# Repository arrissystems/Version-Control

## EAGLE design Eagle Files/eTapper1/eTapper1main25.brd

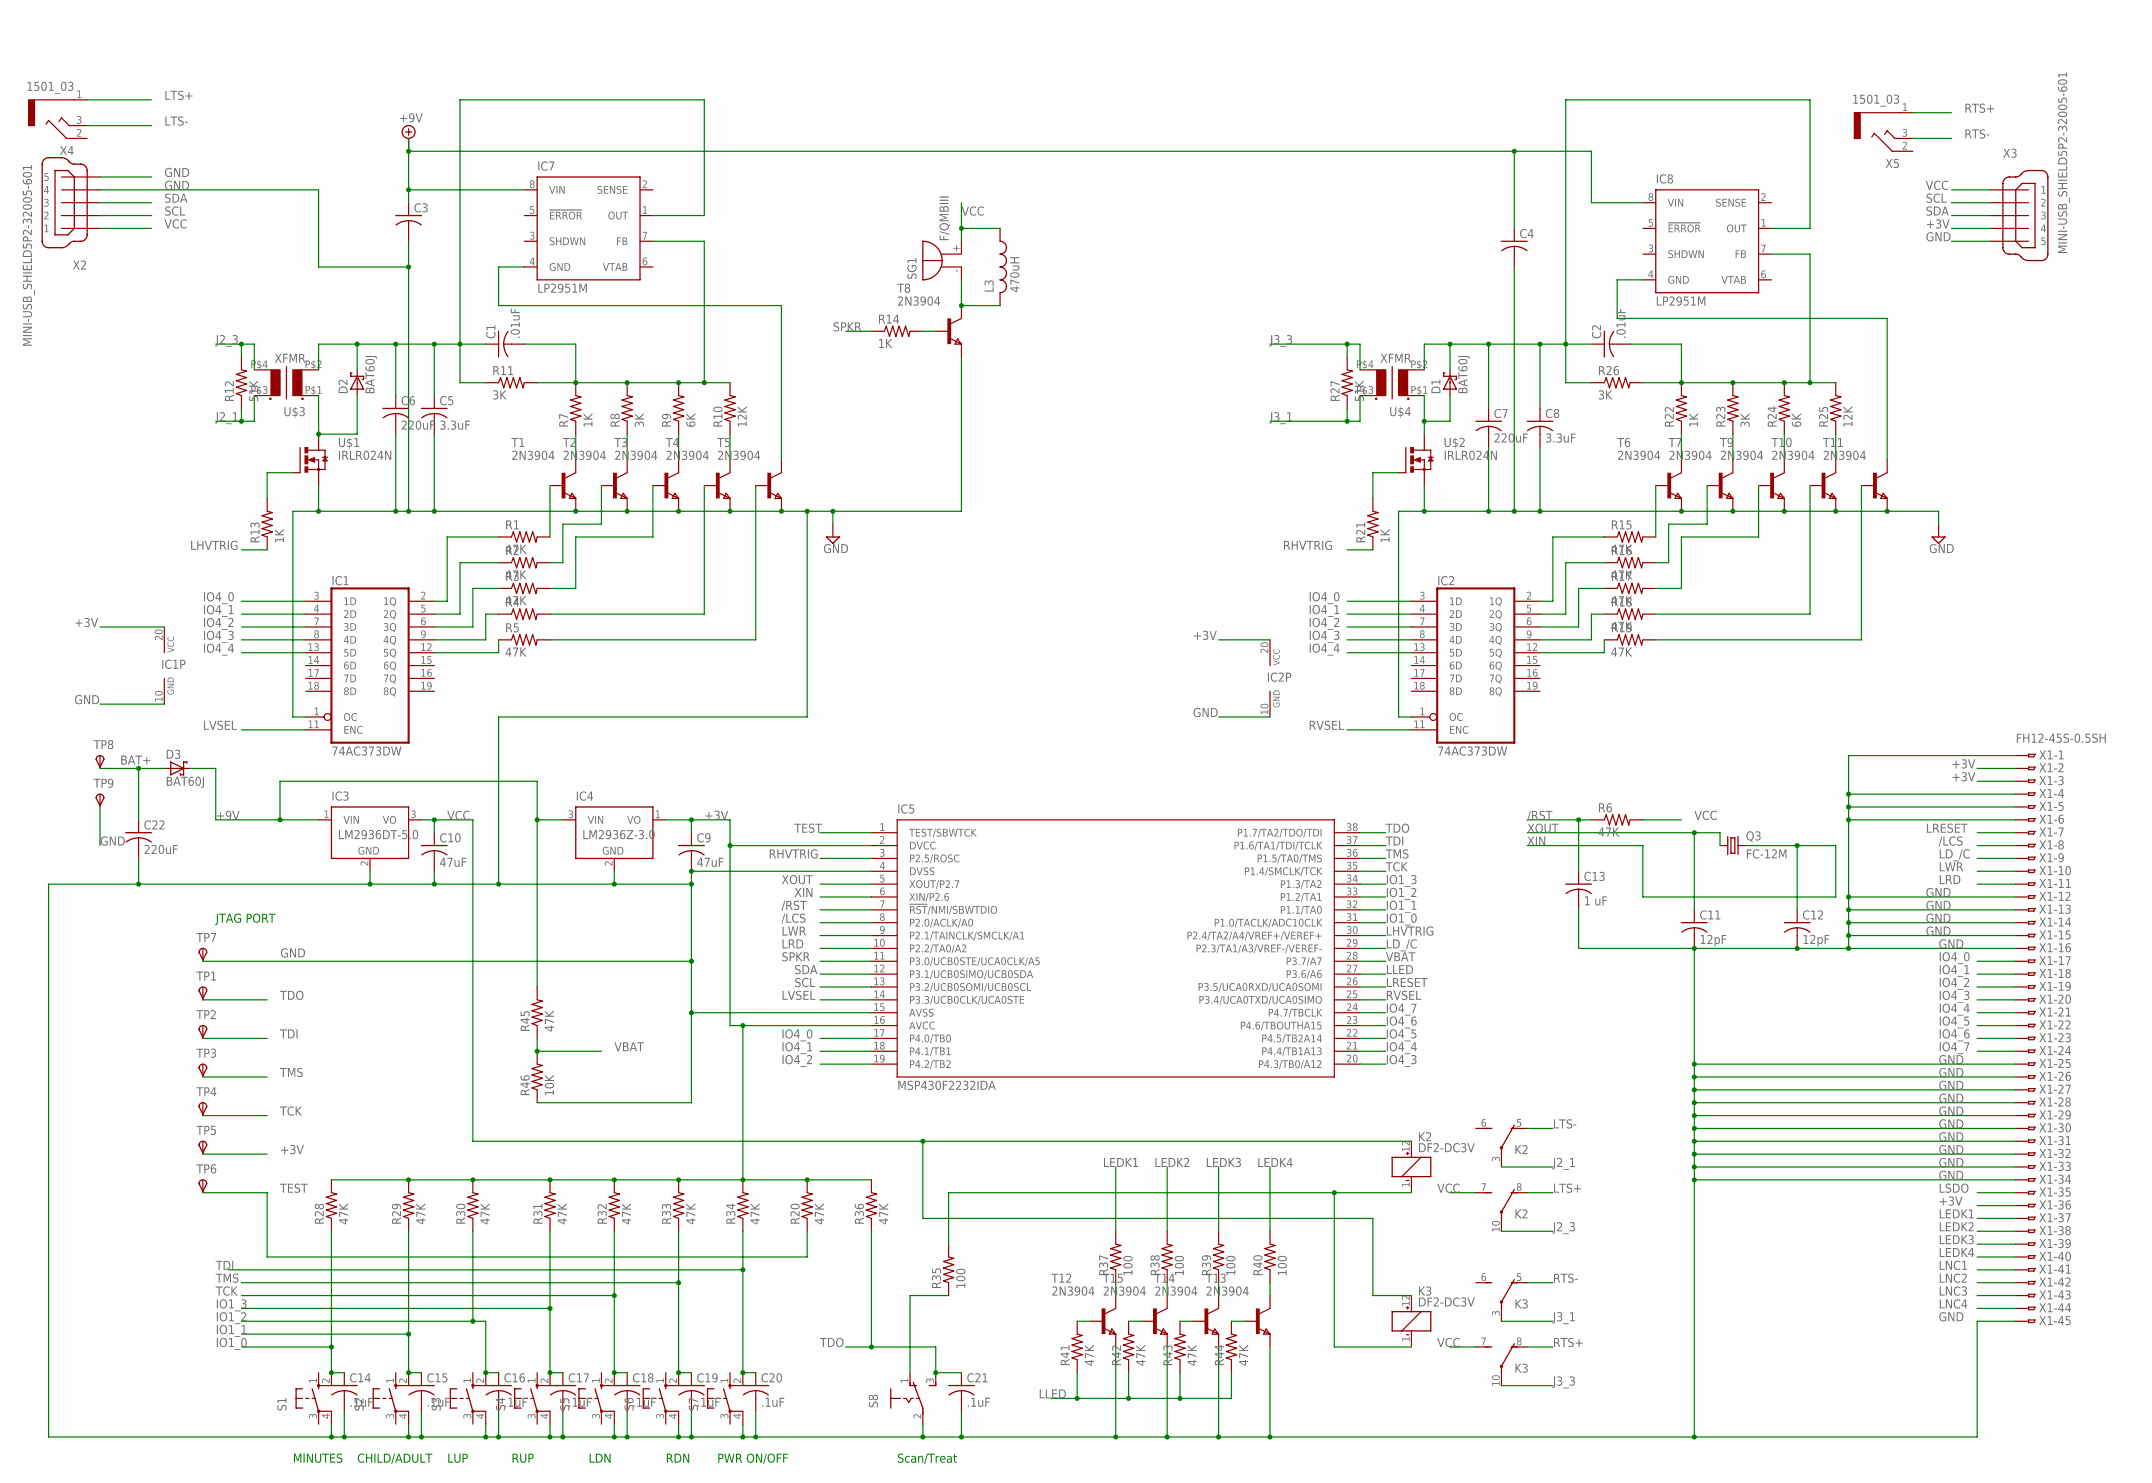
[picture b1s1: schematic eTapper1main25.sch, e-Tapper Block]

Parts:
C1, C2: .01uF; C0805
C3, C4: C-USC0805; C0805
C5, C8: 3.3uF; C0805
C6, C7, C22: 220uF; C0805
C9, C10: 47uF; C0805
C11, C12: 12pF; C0805
C13: 1 uF; C0805
C14, C15, C16, C17, C18, C19, C20, C21: .1uF; C0805
D1, D2, D3: BAT60J; SOD323_ST
IC1, IC2: 74AC373DW; SO20W
IC3: LM2936DT-5.0; TO252
IC4: LM2936Z-3.0; TO92
IC5: MSP430F2232IDA; TSSOP38_R-PDSO-G38-DA
IC7, IC8: LP2951M; SO08
K2, K3: DF2-DC3V; DF2
L3: 470uH; L2825P
Q3: FC-12M
R1, R2, R3, R5, R6, R15, R16, R17, R18, R19, R20, R28, R29, R30, R31, R32, R33, R34, R36, R41, R42, R43, R44, R45: 47K; R0402
R4: R-US_R0402; R0402
R7, R13, R14, R21, R22: 1K; R0402
R8, R11, R23, R26: 3K; R0402
R9, R24: 6K; R0402
R10, R25: 12K; R0402
R12, R27: 51K; R0402
R35, R37, R38, R39, R40: 100; R0402
R46: 10K; R0402
S1, S2, S3, S4, S5, S6, S7: 10-XX; B3F-10XX
S8: M251
SG1: F/QMBIII
T1, T2, T3, T4, T5, T6, T7, T8, T9, T10, T11, T12, T13, T14, T15: 2N3904; SOT-23
TP1, TP2, TP3, TP4, TP5, TP6, TP7, TP8, TP9: TPSTP06R; TP06R
U$1, U$2: IRLR024N; D-PAK_TO252AA
U$3, U$4: XFMR
X1: FH12-45S-0.5SH
X2, X3: MINI-USB_SHIELD5P2-32005-601; 32005-601
X4, X5: 1501_03

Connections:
+3V: C9.1, IC1.20 (VCC), IC2.20 (VCC), IC4.1 (VO), IC5.2 (DVCC), IC5.16 (AVCC), R20.2, R28.2, R29.2, R30.2, R31.2, R32.2, R33.2, R34.2, R36.2, TP5.TP, X1.2, X1.3, X1.36, X3.4
+9V: C3.1, C4.1, D3.C, IC3.1 (VIN), IC4.3 (VIN), IC7.8 (VIN), IC8.8 (VIN), R45.2
/LCS: IC5.8 (P2.0/ACLK/A0), X1.8
/RST: C13.1, IC5.7 (!RST!/NMI/SBWTDIO), R6.1
BAT+: C22.1, D3.A, TP8.TP
GND: C3.2, C4.2, C5.2, C6.2, C7.2, C8.2, C9.2, C10.2, C11.2, C12.2, C13.2, C14.2, C15.2, C16.2, C17.2, C18.2, C19.2, C20.2, C21.2, C22.2, IC1.1 (OC), IC1.10 (GND), IC2.1 (OC), IC2.10 (GND), IC3.2 (GND), IC4.2 (GND), IC5.4 (DVSS), IC5.15 (AVSS), R46.1, S1.4 (P1), S2.4 (P1), S3.4 (P1), S4.4 (P1), S5.4 (P1), S6.4 (P1), S7.4 (P1), S8.2, T1.2 (E), T2.2 (E), T3.2 (E), T4.2 (E), T5.2 (E), T6.2 (E), T7.2 (E), T8.2 (E), T9.2 (E), T10.2 (E), T11.2 (E), T12.2 (E), T13.2 (E), T14.2 (E), T15.2 (E), TP7.TP, TP9.TP, U$1.3 (S), U$2.3 (S), X1.1, X1.4, X1.5, X1.6, X1.12, X1.13, X1.14, X1.15, X1.16, X1.25, X1.26, X1.27, X1.28, X1.29, X1.30, X1.31, X1.32, X1.33, X1.34, X1.45, X2.4, X2.5, X3.5
IO1_0: C14.1, IC5.31 (P1.0/TACLK/ADC10CLK), R28.1, S1.2 (S1)
IO1_1: C15.1, IC5.32 (P1.1/TA0), R29.1, S2.2 (S1)
IO1_2: C16.1, IC5.33 (P1.2/TA1), R30.1, S3.2 (S1)
IO1_3: C17.1, IC5.34 (P1.3/TA2), R31.1, S4.2 (S1)
IO4_0: IC1.3 (1D), IC2.3 (1D), IC5.17 (P4.0/TB0), X1.17
IO4_1: IC1.4 (2D), IC2.4 (2D), IC5.18 (P4.1/TB1), X1.18
IO4_2: IC1.7 (3D), IC2.7 (3D), IC5.19 (P4.2/TB2), X1.19
IO4_3: IC1.8 (4D), IC2.8 (4D), IC5.20 (P4.3/TB0/A12), X1.20
IO4_4: IC1.13 (5D), IC2.13 (5D), IC5.21 (P4.4/TB1A13), X1.21
IO4_5: IC5.22 (P4.5/TB2A14), X1.22
IO4_6: IC5.23 (P4.6/TBOUTHA15), X1.23
IO4_7: IC5.24 (P4.7/TBCLK), X1.24
J2_1: K2.3, R12.1, U$3.P$3 (S1)
J2_3: K2.10, R12.2, U$3.P$4 (S2)
J3_1: K3.3, R27.1, U$4.P$3 (S1)
J3_3: K3.10, R27.2, U$4.P$4 (S2)
LD_/C: IC5.29 (P2.3/TA1/A3/VREF-/VEREF-), X1.9
LEDK1: R37.2, X1.37
LEDK2: R38.2, X1.38
LEDK3: R39.2, X1.39
LEDK4: R40.2, X1.40
LHVTRIG: IC5.30 (P2.4/TA2/A4/VREF+/VEREF+), R13.1
LLED: IC5.27 (P3.6/A6), R41.1, R42.1, R43.1, R44.1
LNC1: X1.41
LNC2: X1.42
LNC3: X1.43
LNC4: X1.44
LRD: IC5.10 (P2.2/TA0/A2), X1.11
LRESET: IC5.26 (P3.5/UCA0RXD/UCA0SOMI), X1.7
LSDO: X1.35
LTS+: K2.8 (O), X4.1
LTS-: K2.5 (O), X4.3
LVSEL: IC1.11 (ENC), IC5.14 (P3.3/UCB0CLK/UCA0STE)
LWR: IC5.9 (P2.1/TAINCLK/SMCLK/A1), X1.10
unnamed: IC1.2 (1Q), R1.1
unnamed: IC1.5 (2Q), R2.1
unnamed: IC1.6 (3Q), R3.1
unnamed: IC1.9 (4Q), R4.1
unnamed: IC1.12 (5Q), R5.1
unnamed: L3.2, SG1.- (+), T8.1 (C)
unnamed: R4.2, T4.3 (B)
unnamed: R5.2, T5.3 (B)
unnamed: D2.A, U$1.4 (D), U$3.P$1 (P1)
unnamed: R7.1, T1.1 (C)
unnamed: R8.1, T2.1 (C)
unnamed: R9.1, T3.1 (C)
unnamed: R1.2, T1.3 (B)
unnamed: R2.2, T2.3 (B)
unnamed: R3.2, T3.3 (B)
unnamed: R10.1, T4.1 (C)
unnamed: C1.2, IC7.7 (FB), R7.2, R8.2, R9.2, R10.2, R11.2
unnamed: C1.1, C5.1, C6.1, D2.C, IC7.1 (OUT), R11.1, U$3.P$2 (P2)
unnamed: D1.A, U$2.4 (D), U$4.P$1 (P1)
unnamed: IC2.2 (1Q), R15.1
unnamed: R13.2, U$1.1 (G)
unnamed: R14.2, T8.3 (B)
unnamed: R35.1, S8.1 (O)
unnamed: IC2.5 (2Q), R16.1
unnamed: IC2.6 (3Q), R17.1
unnamed: IC2.9 (4Q), R18.1
unnamed: IC2.12 (5Q), R19.1
unnamed: R44.2, T13.3 (B)
unnamed: R15.2, T6.3 (B)
unnamed: R16.2, T7.3 (B)
unnamed: R17.2, T9.3 (B)
unnamed: R18.2, T10.3 (B)
unnamed: R19.2, T11.3 (B)
unnamed: K2.1 (-), K3.1 (-), R35.2
unnamed: R22.1, T6.1 (C)
unnamed: R23.1, T7.1 (C)
unnamed: R24.1, T9.1 (C)
unnamed: R25.1, T10.1 (C)
unnamed: C2.2, IC8.7 (FB), R22.2, R23.2, R24.2, R25.2, R26.2
unnamed: C2.1, C7.1, C8.1, D1.C, IC8.1 (OUT), R26.1, U$4.P$2 (P2)
unnamed: R37.1, T12.1 (C)
unnamed: R21.2, U$2.1 (G)
unnamed: R38.1, T15.1 (C)
unnamed: R39.1, T14.1 (C)
unnamed: IC7.4 (GND), T5.1 (C)
unnamed: R40.1, T13.1 (C)
unnamed: IC8.4 (GND), T11.1 (C)
unnamed: R43.2, T14.3 (B)
unnamed: R41.2, T12.3 (B)
unnamed: R42.2, T15.3 (B)
RHVTRIG: IC5.3 (P2.5/ROSC), R21.1
RTS+: K3.8 (O), X5.1
RTS-: K3.5 (O), X5.3
RVSEL: IC2.11 (ENC), IC5.25 (P3.4/UCA0TXD/UCA0SIMO)
SCL: IC5.13 (P3.2/UCB0SOMI/UCB0SCL), X2.2, X3.2
SDA: IC5.12 (P3.1/UCB0SIMO/UCB0SDA), X2.3, X3.3
SPKR: IC5.11 (P3.0/UCB0STE/UCA0CLK/A5), R14.1
TCK: C18.1, IC5.35 (P1.4/SMCLK/TCK), R32.1, S5.2 (S1), TP4.TP
TDI: C20.1, IC5.37 (P1.6/TA1/TDI/TCLK), R34.1, S7.2 (S1), TP2.TP
TDO: C21.1, IC5.38 (P1.7/TA2/TDO/TDI), R36.1, S8.3 (S), TP1.TP
TEST: IC5.1 (TEST/SBWTCK), R20.1, TP6.TP
TMS: C19.1, IC5.36 (P1.5/TA0/TMS), R33.1, S6.2 (S1), TP3.TP
VBAT: IC5.28 (P3.7/A7), R45.1, R46.2
VCC: C10.1, IC3.3 (VO), K2.7 (S), K2.12 (+), K3.7 (S), K3.12 (+), L3.1, R6.2, SG1.+ (-), X2.1, X3.1
XIN: C12.1, IC5.6 (XIN/P2.6), Q3.2
XOUT: C11.1, IC5.5 (XOUT/P2.7), Q3.1

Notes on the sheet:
PWR ON/OFF
Scan/Treat
MINUTES
CHILD/ADULT
LUP
RUP
JTAG PORT
LDN
RDN

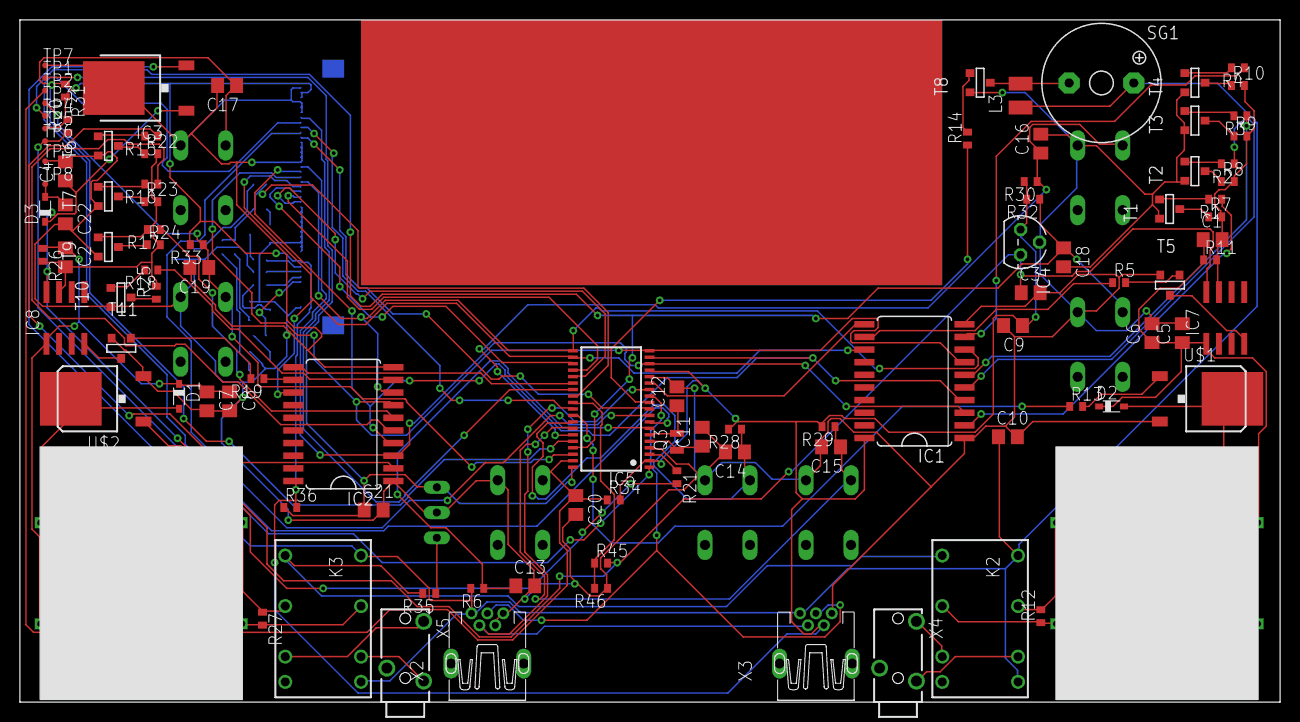
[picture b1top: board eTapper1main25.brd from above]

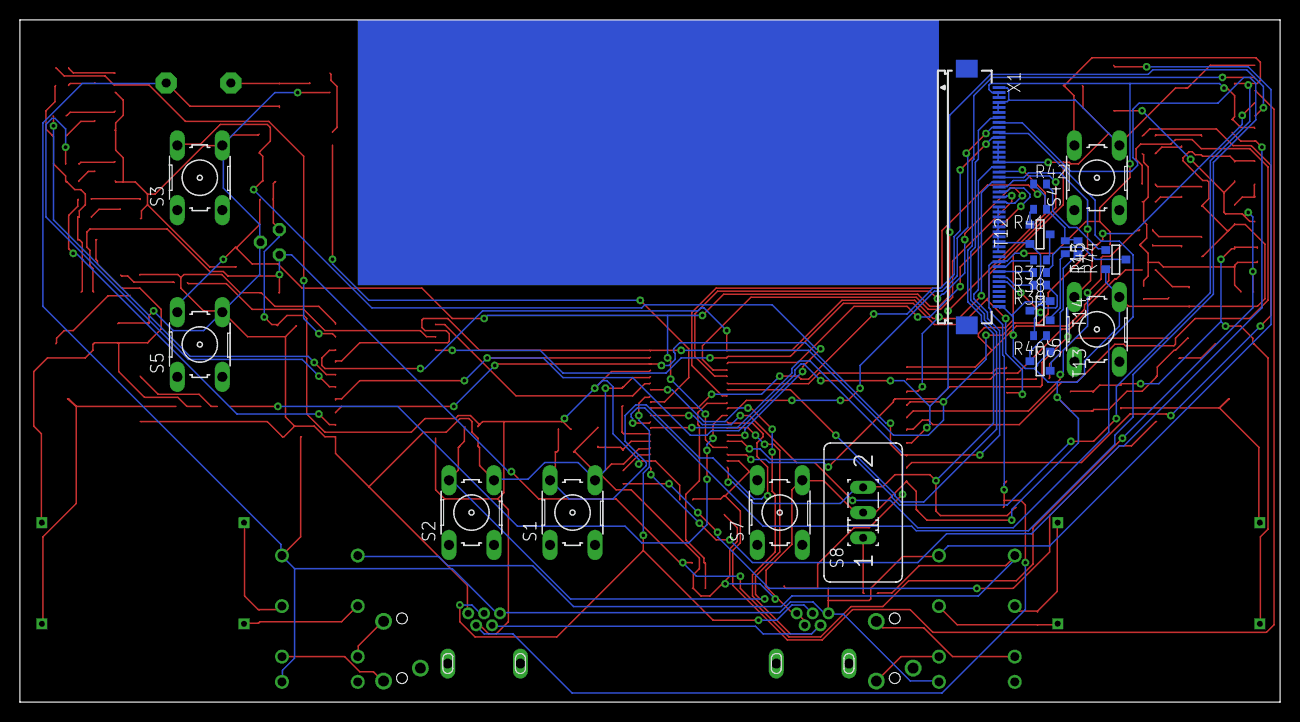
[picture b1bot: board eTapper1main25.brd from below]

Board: 2 copper layers, 126.7 x 68.6 mm, 124 parts (21 on the bottom side), 101 nets.
